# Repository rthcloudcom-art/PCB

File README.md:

# AgriNode — سخت‌افزار IoT برای مدیریت هوشمند کشاورزی و دامپروری

خانواده‌ای از بردهای الکترونیکی برای کنترل، مانیتورینگ و مدیریت **گلخانه، مرغداری، دامداری،
پرورش ماهی، مزرعه و باغ**.

| سند | محتوا |
|---|---|
| [`docs/01-features.md`](docs/01-features.md) | فاز ۱ — فهرست جامع قابلیت‌ها برای هر کاربری و ترجمه‌ی آن به نیازمندی سخت‌افزاری |
| [`docs/02-architecture.md`](docs/02-architecture.md) | فاز ۲ — معماری (نودها + هاب)، تغذیه، قوانین ساخت برای دستگاه کم‌دقت، اقدامات صنعتی |
| [`docs/03-roadmap.md`](docs/03-roadmap.md) | فاز ۳ — نقشه‌ی راه بردهای بعدی |
| [`docs/portfolio/`](docs/portfolio/README.md) | **سبد محصولات** (نسخه‌بندی‌شده) — کنترلر، برد قدرت، نود بی‌سیم، پروب هوشمند و راهکار ۱۵ صنعت؛ نسخه‌ی فعلی: v2 (در حال بررسی) |
| [`hardware/hubs/`](hardware/hubs/README.md) | **بردهای هاب** — HUB-W (Wi-Fi)، HUB-L (LoRa)، HUB-C (4G LTE)، GW-LAN (گیت‌وی LoRa→LAN)؛ هر کدام یک برد دو لایه‌ی جدا با هسته‌ی مشترک |
| [`hardware/lib/`](hardware/lib) | کتابخانه‌ی سمبل و فوت‌پرینت برای ساخت با دستگاه کم‌دقت (پدهای باریک‌شده، فاصله ≥ 0.55mm) |
| [`hardware/archive/mc1-4layer/`](hardware/archive/mc1-4layer/README.md) | نسخه‌ی قبلی (برد یکپارچه‌ی ۴ لایه، کنار گذاشته شد) |
| [`hardware/archive/hub1-universal-2layer/`](hardware/archive/hub1-universal-2layer/README.md) | نسخه‌ی قبلی هاب (یک برد برای همه‌ی انواع، کنار گذاشته شد) |

## ساختار مخزن

```
docs/                      اسناد نیازمندی و معماری
hardware/<board>/
    design/*.py            منبع طراحی مدار (پایتون)
    build.py               تولید شماتیک KiCad + بررسی نت‌لیست + BOM + PDF
    pcb.py                 تولید PCB (چیدمان، زون‌ها، قوانین، مسیریابی خودکار)
    kicad/                 پروژه‌ی KiCad تولیدشده
    outputs/               PDF شماتیک، BOM، گزارش DRC، تصاویر
tools/kigen/               کتابخانه‌ی کوچک «مدار به صورت کد» برای تولید فایل‌های KiCad
```

## پیش‌نیازها

- KiCad 7 یا جدیدتر (کتابخانه‌های رسمی symbol و footprint)
- Python 3.10+ (ماژول `pcbnew` که همراه KiCad نصب می‌شود)
- برای مسیریابی خودکار: Java 25 و [Freerouting](https://github.com/freerouting/freerouting) 2.4+
  (`FREEROUTING_JAR` و `FREEROUTING_JAVA` را تنظیم کنید)

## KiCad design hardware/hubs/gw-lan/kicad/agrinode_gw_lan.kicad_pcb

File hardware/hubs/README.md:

# بردهای هاب AgriNode (rev A)

هر نوع هاب یک **برد کوچک جداگانه** است. همه‌ی بردها یک **هسته‌ی مشترک** دارند (مدار و جای قطعات یکسان در
100 میلی‌متر سمت چپ برد) و فقط **بلوک ارتباطی** سمت راست برد فرق می‌کند. همه **دو لایه** با قوانین درشت
برای دستگاه کم‌دقت هستند (چرا دو لایه؟ [`docs/02-architecture.md`](../../docs/02-architecture.md#۵-چرا-بردهای-هاب-دو-لایه‌اند)).

| برد | پوشه | کاربرد | بلوک ارتباطی | ابعاد |
|---|---|---|---|---|
| **HUB-W** | [`hub-w/`](hub-w) | نودها ← Wi-Fi ← هاب ← Wi-Fi مودم | — (فقط هسته) | 114 × 96 mm |
| **HUB-L** | [`hub-l/`](hub-l) | هاب با ارسال LoRa به نقطه‌ی دور | Ra-02 (SX1278، 433MHz) | 130 × 96 mm |
| **HUB-C** | [`hub-c/`](hub-c) | هاب با سیم‌کارت 4G | هدر برد ماژول LTE (A7670E / EC200U) | 130 × 108 mm |
| **GW-LAN** | [`gw-lan/`](gw-lan) | گیرنده‌ی LoRa در ساختمان + کابل شبکه به مودم | Ra-02 + ENC28J60 + RJ45 | 150 × 108 mm |

آنتن PCB ماژول ESP32 حدود 6 میلی‌متر از لبه‌ی بالای برد بیرون می‌زند (برای برد Wi-Fi بهترین حالت است)؛
در جعبه جای آن را در نظر بگیرید.

## هسته‌ی مشترک

| بلوک | قطعه‌ی اصلی | توضیح |
|---|---|---|
| پردازنده | ESP32-WROOM-32E-N8 | Wi-Fi + BLE؛ ارتباط با نودها با ESP-NOW یا Wi-Fi |
| ورودی تغذیه | جک 5.5/2.1 و ترمینال 12V (7..24V)، ترمینال پنل خورشیدی 6..24V، USB-B 5V | هر ورودی: فیوز PTC، دیود معکوس، TVS |
| مبدل 5V | LM2596S-5 (ورودی 7..40V، 3A) | |
| شارژر | TP4056 (1A) + NTC دمای باتری | شارژ فقط بین 0 تا 45 درجه؛ بدون NTC جامپر `JP1` را لحیم کنید |
| باتری | 18650 **دارای مدار حفاظت** در جاباتری سوراخ‌دار | PTC + ماسفت حفاظت جاگذاری برعکس |
| مسیر توان | دیود + AO3401 | با وجود برق از 5V، در قطع برق بدون وقفه از باتری (UPS) |
| 3.3V | MIC29302 (افت ولتاژ کم، 3A) | |
| ساعت | **DS3231M** + باتری سکه‌ای CR2032 | زمان دقیق برای برچسب زمانی داده‌ها و زمان‌بندی، حتی بدون اینترنت و در قطع برق |
| پورت پروگرام | **USB-B** با CH340C + ریست/بوت خودکار | همان کابل USB هم برق می‌دهد هم پروگرام می‌کند (Arduino / ESP-IDF بدون فشار دکمه) |
| هدر PROG | 6 پین: `1 GND  2 TXD0  3 RXD0  4 3V3  5 EN  6 IO0` | برای مبدل USB-سریال بیرونی (مقاومت‌های 1k سری اجازه می‌دهند هدر بر CH340C غلبه کند) |
| دکمه‌ها | **RESET** و **BOOT / PAIR** (6×6 سوراخ‌دار) | BOOT هنگام روشن‌شدن = حالت پروگرام؛ در کار عادی = جفت‌سازی نود |
| LED وضعیت | هدر 4 پین برای **نوار LED آدرس‌پذیر WS2813** | پایین را ببینید |
| بازر | بازر مغناطیسی 5V با ترانزیستور | آلارم محلی |
| I²C | هدر 4 پین: `1 GND  2 3V3  3 SCL  4 SDA` | نمایشگر OLED یا سنسور اضافه |
| **RS-485 (اختیاری)** | MAX3485 + SM712 + ترمینال 3 پین | Modbus RTU برای سنسورهای صنعتی سیمی تا 1 km؛ اگر لازم نیست قطعات بلوک را لحیم نکنید (`bom_without_rs485.csv`) |

### چرا RTC و RS-485؟

- **RTC**: هاب داده‌ها را هنگام قطع اینترنت بافر می‌کند؛ بدون ساعت پشتیبان، بعد از قطع برق زمان داده‌ها گم
  می‌شود. DS3231M دقت ±5ppm دارد و با CR2032 سال‌ها کار می‌کند.
- **RS-485**: بسیاری از سنسورهای صنعتی (خاک 7-in-1، pH/EC، ایستگاه هواشناسی، کنتور برق، اینورتر) فقط
  Modbus RTU دارند؛ این کابل تا 1 کیلومتر در محیط پرنویز کار می‌کند. هاب می‌تواند سنسورهای نزدیک خودش را
  مستقیم بخواند. مقاومت پایان خط 120Ω با جامپر `JP2` (فقط روی آخرین دستگاه خط) وصل می‌شود.

### نوار LED وضعیت (WS2813)

هدر `LED STRIP WS2813`: `1 VLED  2 DIN  3 GND  4 GND`

- LEDها به صورت **نواری** پشت سر هم وصل می‌شوند (DO هر LED به DI بعدی) و روی پنل جعبه نصب می‌شوند.
- داده از GPIO27 با مبدل سطح BSS138 به 5V و مقاومت سری 330Ω؛ VLED از VSYS با فیوز PTC 0.75A
  (حدود 10 LED با حداکثر روشنایی سفید؛ برای وضعیت، روشنایی کم کافی است).
- WS2813 ورودی پشتیبان (BI) دارد: اگر یک LED خراب شود بقیه کار می‌کنند. BI اولین LED را به GND وصل کنید.
- هنگام کار با باتری، VLED حدود 3.3..4.2V است؛ WS2813 کار می‌کند ولی رنگ آبی/سفید کم‌نورتر است.

ترتیب پیشنهادی LEDها در فریم‌ور:

| LED | معنی | رنگ‌ها |
|---|---|---|
| 1 | تغذیه/باتری | سبز: برق شبکه · زرد: روی باتری · قرمز: باتری ضعیف · آبی چشمک‌زن: در حال شارژ |
| 2 | Wi-Fi و نودها | سبز: وصل · زرد: بعضی نودها قطع · قرمز: قطع |
| 3 | ارتباط بیرونی (Wi-Fi مودم / LoRa / 4G / LAN) | سبز: وصل · آبی چشمک: ارسال · قرمز: قطع |
| 4 | LoRa / LAN (فقط GW-LAN) | سبز چشمک: دریافت بسته · زرد: لینک LAN بدون اینترنت |
| 5 | آلارم | خاموش: عادی · قرمز چشمک: آلارم فعال |
| 6 | سیستم | سبز: عادی · بنفش: حالت جفت‌سازی · سفید: به‌روزرسانی فریم‌ور |

## بلوک‌های ارتباطی

### HUB-L و GW-LAN: LoRa

Ai-Thinker **Ra-02** (SX1278، 433MHz، تا 20dBm) روی SPI؛ آنتن با کابل IPEX به SMA روی جعبه.
GW-LAN در ساختمان قرار می‌گیرد، بسته‌های HUB-L را دریافت می‌کند و با **ENC28J60** (10BASE-T) و جک
مگنتیک HR911105A با کابل LAN به مودم می‌فرستد.

### HUB-C: برد ماژول 4G LTE

به‌جای لحیم ماژول سلولار روی برد (پدهای LGA ظریف که با دستگاه کم‌دقت قابل ساخت نیست)، یک **برد آماده‌ی
ماژول LTE** (برای کارخانه/محیط صنعتی: SIMCom **A7670E** یا Quectel **EC200U**، LTE Cat-1 با پشتیبانی 2G)
روی هدر 8 پین نصب می‌شود. این بردها سیم‌کارت، آنتن و مدار راه‌اندازی مودم را خودشان دارند.

هدر `LTE MODULE` (1×8، 2.54mm):

| پین | نام | توضیح |
|---|---|---|
| 1 | VMOD_5V | 5V قابل قطع (AO3401) — برای بردهایی که رگولاتور خودشان را دارند؛ فقط وقتی برق بیرونی وصل است |
| 2 | VMOD_4V | 4.0V / 3A قابل قطع (MIC29302، خازن 1000µF) — برای اتصال مستقیم به VBAT ماژول |
| 3، 4 | GND | |
| 5 | MOD_TXD | خروجی داده‌ی مودم ← GPIO19 (با 1k سری) |
| 6 | MOD_RXD | ورودی داده‌ی مودم ← GPIO23 (با 1k سری) |
| 7 | MOD_PWRKEY | کلید روشن/خاموش مودم (کلکتور باز، فعال-پایین) — GPIO21 |
| 8 | MOD_STATUS | وضعیت روشن‌بودن مودم ← GPIO18 |

- **فقط یکی** از پین‌های 1 یا 2 را به ورودی تغذیه‌ی برد ماژول وصل کنید (مطابق دیتاشیت همان برد).
- سطح منطقی UART باید **3.3V** باشد (بیشتر بردهای A7670E/EC200U مبدل سطح دارند؛ اگر پین سطح IO دارد
  آن را به 3.3V ببندید).
- ESP32 با GPIO22 تغذیه‌ی مودم را کامل قطع و وصل می‌کند (راه‌اندازی دوباره‌ی مودم هنگ‌کرده بدون حضور اپراتور).

## نقشه‌ی پایه‌های ESP32

پایه‌ها طوری انتخاب شده‌اند که هر سیگنال از سمتی از ماژول خارج شود که قطعه‌اش آنجاست (ستون راست ماژول رو به
RS-485 و بلوک ارتباطی، ستون چپ رو به تغذیه و پنل جلو، ردیف پایین رو به شارژر) تا مسیرها کوتاه و بدون تقاطع باشند.

**هسته (همه‌ی بردها):**

| GPIO | کاربرد | GPIO | کاربرد |
|---|---|---|---|
| 0 | دکمه BOOT/PAIR (+ ریست خودکار) | 27 | داده‌ی نوار LED |
| 1 / 3 | TX0 / RX0 (CH340C و هدر PROG) | 33 / 32 | I²C SDA / SCL (RTC و هدر I2C) |
| 2 | بازر | 34 | ولتاژ باتری (ADC) |
| 13 | وضعیت شارژ `CHRG` | 35 | ولتاژ ورودی DC/خورشیدی (ADC) |
| 17 / 16 / 4 | RS-485 TX / RX / DE | EN | ریست (دکمه، ریست خودکار، هدر PROG) |

**بلوک ارتباطی:**

| GPIO | HUB-L | GW-LAN | HUB-C |
|---|---|---|---|
| 18 | SPI SCK | SPI SCK | STATUS مودم (ورودی) |
| 19 | SPI MISO | SPI MISO | UART مودم RX |
| 23 | SPI MOSI | SPI MOSI | UART مودم TX |
| 5 | LoRa CS | LoRa CS | — |
| 21 | LoRa DIO0 | LoRa DIO0 | PWRKEY مودم |
| 22 | ریست LoRa | ENC28J60 CS | روشن‌کردن تغذیه‌ی مودم |
| 14 | — | ریست LoRa | — |
| 36 (VP) | — | وقفه‌ی ENC28J60 | — |

پایه‌های آزاد روی هر برد (مثلاً 12، 15، 25، 26، 39) برای توسعه‌ی بعدی خالی مانده‌اند.

## ساخت برد

- **دو لایه**، ضخامت 1.6mm، مس 35µm؛ ترک سیگنال 0.5mm، تغذیه 0.7..0.8mm، فاصله 0.5mm، ویا 0.6mm
  سوراخ / 1.2mm پد (اگر برد را خودتان می‌سازید، ویاها را با سیم مسی نازک از دو طرف لحیم کنید).
- همه‌ی قطعات در **سمت رو**؛ SMD فقط 1206، SOT-23، SOT-223، SOIC، TO-263 (بدون QFN/TSSOP/0603).
- صفحه‌ی زمین (GND pour) در هر دو لایه؛ زیر آنتن ESP32 مس و ترک ممنوع است.
- پس از مونتاژ و تست، **کوتینگ محافظ** (Conformal Coating) بزنید؛ کانکتورها، دکمه‌ها و هدرها را ماسک کنید.
- فایل‌های ساخت: `python3 export_fab.py <variant>` → `<variant>/outputs/fab/` و فایل zip.

## وضعیت فعلی PCB

| برد | مسیریابی | جامپر سیمی | DRC | خروجی‌ها |
|---|---|---|---|---|
| HUB-W | کامل | ندارد | 0 خطای فاصله/اتصال (فقط هشدار سیلک‌اسکرین و اسپوک حرارتی) | تصاویر + Gerber |
| HUB-L | کامل به‌جز 1 اتصال | **W1** (11 mm، مدار ریست خودکار: R19 پد 2 ← پایه‌ی بیس Q3) | 0 خطای فاصله | تصاویر + Gerber |
| HUB-C | کامل | ندارد | 0 خطای فاصله/اتصال | تصاویر + Gerber |
| GW-LAN | کامل | ندارد | 0 خطای فاصله/اتصال | تصاویر + Gerber |

**جامپر سیمی:** اتصالی که مسیریاب نتوانسته کامل کند با یک سیم روکش‌دار نازک (مثلاً سیم wire-wrap) در سمت رو
لحیم می‌شود؛ دو سر آن روی سیلک‌اسکرین با `W1`، `W2`… علامت خورده و فهرستش در `<variant>/outputs/jumpers.txt` است
(طبق توافق، حداکثر یکی دو جامپر).

**نکته‌ی هشدارهای DRC باقی‌مانده:** `silk_*` (متن سیلک نزدیک لبه یا روی هم) و `starved_thermal` (پد زمینی که
با یک اسپوک به صفحه‌ی زمین وصل شده) هیچ‌کدام اشکال الکتریکی نیستند. `lib_footprint_mismatch` روی جک RJ45 (و
در نسخه‌های قبلی USB-B) عمدی است: حلقه‌ی مسی پدهای سوراخ‌دار برای سوراخ‌کاری درشت به ≥ 0.26 mm بزرگ شده است.

## فایل‌ها

| مسیر | توضیح |
|---|---|
| `design/hubs.py` | منبع طراحی مدار (هسته + بلوک هر نوع) |
| `build.py <variant>` | تولید شماتیک KiCad، بررسی نت‌لیست، BOMها، PDF |
| `pcb.py <variant> [--route]` | چیدمان، قوانین، مسیریابی خودکار (Freerouting + مسیریاب تکمیلی)، DRC |
| `route_search.py <variant>` | چند تنظیم هزینه‌ی Freerouting را امتحان می‌کند و بهترین برد (کمترین اتصال باز، بدون خطای فاصله) را نگه می‌دارد |
| `render.py <variant>` | تصاویر `pcb_top.png`، `pcb_bottom.png`، `pcb_assembly.png` |
| `export_fab.py <variant>` | Gerber و Drill |
| `<variant>/kicad/` | پروژه‌ی KiCad (کتابخانه‌های `hardware/lib` از طریق جدول کتابخانه‌ی پروژه) |
| `<variant>/outputs/` | PDF شماتیک، `bom.csv` (ستون Option)، `bom_without_rs485.csv`، گزارش DRC، تصاویر، Gerber |

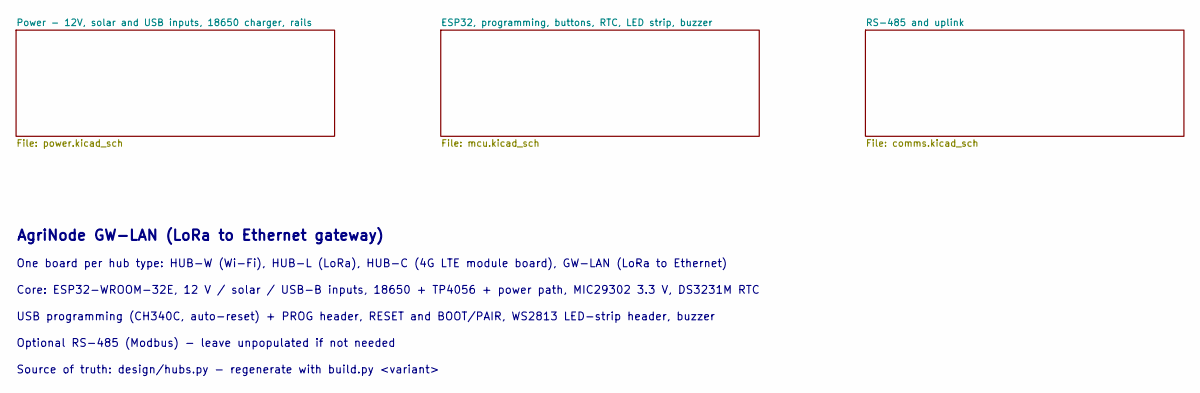
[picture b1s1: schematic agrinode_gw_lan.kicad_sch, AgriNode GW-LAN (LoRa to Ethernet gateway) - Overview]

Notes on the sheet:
AgriNode GW-LAN (LoRa to Ethernet gateway)
One board per hub type: HUB-W (Wi-Fi), HUB-L (LoRa), HUB-C (4G LTE module board), GW-LAN (LoRa to Ethernet)
Core: ESP32-WROOM-32E, 12 V / solar / USB-B inputs, 18650 + TP4056 + power path, MIC29302 3.3 V, DS3231M RTC
USB programming (CH340C, auto-reset) + PROG header, RESET and BOOT/PAIR, WS2813 LED-strip header, buzzer
Optional RS-485 (Modbus) - leave unpopulated if not needed
Source of truth: design/hubs.py - regenerate with build.py <variant>

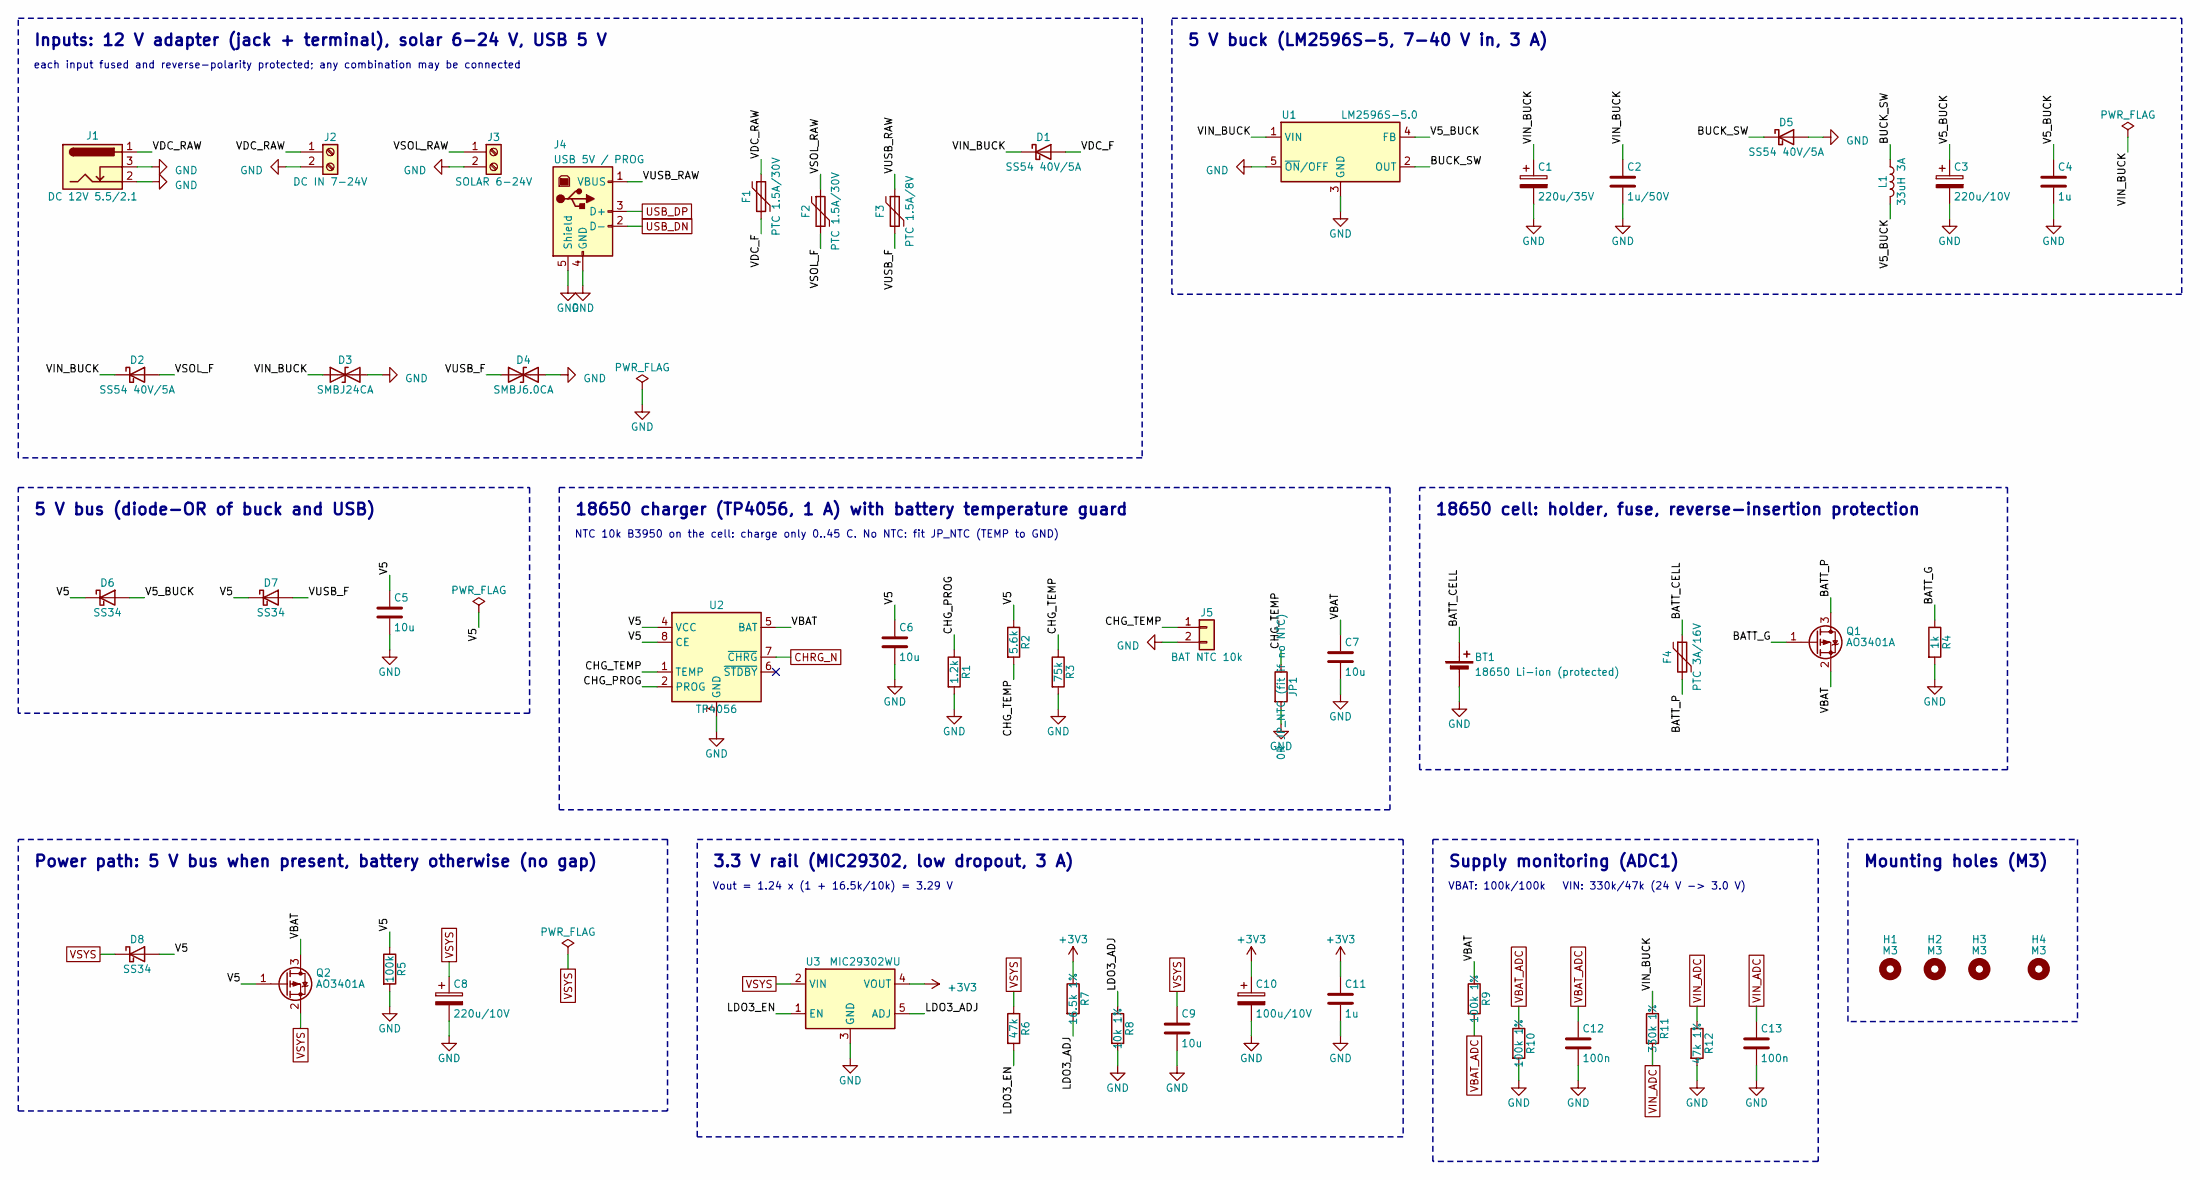
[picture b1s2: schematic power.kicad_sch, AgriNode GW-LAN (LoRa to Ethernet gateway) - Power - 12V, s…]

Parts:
BT1: 18650 Li-ion (protected); BatteryHolder_MPD_BH-18650-PC2
C1: 220u/35V; CP_Radial_D8.0mm_P3.50mm
C2: 1u/50V; C_1206_3216Metric
C3, C8: 220u/10V; CP_Radial_D8.0mm_P3.50mm
C4, C11: 1u; C_1206_3216Metric
C5, C6, C7, C9: 10u; C_1206_3216Metric
C10: 100u/10V; CP_Radial_D8.0mm_P3.50mm
C12, C13: 100n; C_1206_3216Metric
D1, D2, D5: SS54 40V/5A; D_SMC
D3: SMBJ24CA; D_SMB
D4: SMBJ6.0CA; D_SMB
D6, D7, D8: SS34; D_SMA
F1, F2: PTC 1.5A/30V; Fuse_1812_4532Metric
F3: PTC 1.5A/8V; Fuse_1812_4532Metric
F4: PTC 3A/16V; Fuse_1812_4532Metric
H1, H2, H3, H4: M3; MountingHole_3.2mm_M3
J1: DC 12V 5.5/2.1; BarrelJack_Horizontal
J2: DC IN 7-24V; TerminalBlock_Phoenix_MKDS-1,5-2-5.08_1x02_P5.08mm_Horizont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
J3: SOLAR 6-24V; TerminalBlock_Phoenix_MKDS-1,5-2-5.08_1x02_P5.08mm_Horizont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
J4: USB 5V / PROG; USB_B_THT_Coarse
J5: BAT NTC 10k; PinHeader_1x02_P2.54mm_Vertical
JP1: 0R JP_NTC (fit if no NTC); R_1206_3216Metric
L1: 33uH 3A; L_12x12mm_H6mm
Q1, Q2: AO3401A; SOT-23
R1: 1.2k; R_1206_3216Metric
R2: 5.6k; R_1206_3216Metric
R3: 75k; R_1206_3216Metric
R4: 1k; R_1206_3216Metric
R5: 100k; R_1206_3216Metric
R6: 47k; R_1206_3216Metric
R7: 16.5k 1%; R_1206_3216Metric
R8: 10k 1%; R_1206_3216Metric
R9, R10: 100k 1%; R_1206_3216Metric
R11: 330k 1%; R_1206_3216Metric
R12: 47k 1%; R_1206_3216Metric
U1: LM2596S-5.0; TO-263-5_TabPin3
U2: TP4056; ESOP-8_TP4056_Coarse
U3: MIC29302WU; TO-263-5_TabPin3

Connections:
+3V3: C10.1, C11.1, R7.1, U3.4 (VOUT); also elsewhere on the board
/Power - 12V, solar and USB inputs, 18650 charger, rails/BATT_CELL: BT1.1 (+), F4.1
/Power - 12V, solar and USB inputs, 18650 charger, rails/BATT_G: Q1.1 (G), R4.1
/Power - 12V, solar and USB inputs, 18650 charger, rails/BATT_P: F4.2, Q1.3 (D)
/Power - 12V, solar and USB inputs, 18650 charger, rails/BUCK_SW: D5.1 (K), L1.1, U1.2 (OUT)
/Power - 12V, solar and USB inputs, 18650 charger, rails/CHG_PROG: R1.1, U2.2 (PROG)
/Power - 12V, solar and USB inputs, 18650 charger, rails/CHG_TEMP: J5.1, JP1.1, R2.2, R3.1, U2.1 (TEMP)
/Power - 12V, solar and USB inputs, 18650 charger, rails/LDO3_ADJ: R7.2, R8.1, U3.5 (ADJ)
/Power - 12V, solar and USB inputs, 18650 charger, rails/LDO3_EN: R6.2, U3.1 (EN)
/Power - 12V, solar and USB inputs, 18650 charger, rails/V5: C5.1, C6.1, D6.1 (K), D7.1 (K), D8.2 (A), Q2.1 (G), R2.1, R5.1, U2.4 (VCC), U2.8 (CE)
/Power - 12V, solar and USB inputs, 18650 charger, rails/V5_BUCK: C3.1, C4.1, D6.2 (A), L1.2, U1.4 (FB)
/Power - 12V, solar and USB inputs, 18650 charger, rails/VBAT: C7.1, Q1.2 (S), Q2.3 (D), R9.1, U2.5 (BAT)
/Power - 12V, solar and USB inputs, 18650 charger, rails/VDC_F: D1.2 (A), F1.2
/Power - 12V, solar and USB inputs, 18650 charger, rails/VDC_RAW: F1.1, J1.1, J2.1
/Power - 12V, solar and USB inputs, 18650 charger, rails/VIN_BUCK: C1.1, C2.1, D1.1 (K), D2.1 (K), D3.1 (A1), R11.1, U1.1 (VIN)
/Power - 12V, solar and USB inputs, 18650 charger, rails/VSOL_F: D2.2 (A), F2.2
/Power - 12V, solar and USB inputs, 18650 charger, rails/VSOL_RAW: F2.1, J3.1
/Power - 12V, solar and USB inputs, 18650 charger, rails/VUSB_F: D4.1 (A1), D7.2 (A), F3.2
/Power - 12V, solar and USB inputs, 18650 charger, rails/VUSB_RAW: F3.1, J4.1 (VBUS)
CHRG_N: U2.7 (~CHRG); also elsewhere on the board
GND: BT1.2 (-), C1.2, C2.2, C3.2, C4.2, C5.2, C6.2, C7.2, C8.2, C9.2, C10.2, C11.2, C12.2, C13.2, D3.2 (A2), D4.2 (A2), D5.2 (A), J1.2, J1.3, J2.2, J3.2, J4.4 (GND), J4.5 (Shield), J5.2, JP1.2, R1.2, R3.2, R4.2, R5.2, R8.2, R10.2, R12.2, U1.3 (GND), U1.5 (~ON/OFF), U2.3 (GND), U2.9 (GND), U3.3 (GND); also elsewhere on the board
USB_DN: J4.2 (D-); also elsewhere on the board
USB_DP: J4.3 (D+); also elsewhere on the board
VBAT_ADC: C12.1, R9.2, R10.1; also elsewhere on the board
VIN_ADC: C13.1, R11.2, R12.1; also elsewhere on the board
VSYS: C8.1, C9.1, D8.1 (K), Q2.2 (S), R6.1, U3.2 (VIN); also elsewhere on the board

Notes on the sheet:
Inputs: 12 V adapter (jack + terminal), solar 6-24 V, USB 5 V
each input fused and reverse-polarity protected; any combination may be connected
5 V buck (LM2596S-5, 7-40 V in, 3 A)
5 V bus (diode-OR of buck and USB)
18650 charger (TP4056, 1 A) with battery temperature guard
NTC 10k B3950 on the cell: charge only 0..45 C. No NTC: fit JP_NTC (TEMP to GND)
18650 cell: holder, fuse, reverse-insertion protection
Power path: 5 V bus when present, battery otherwise (no gap)
3.3 V rail (MIC29302, low dropout, 3 A)
Vout = 1.24 x (1 + 16.5k/10k) = 3.29 V
Supply monitoring (ADC1)
VBAT: 100k/100k VIN: 330k/47k (24 V -> 3.0 V)
Mounting holes (M3)

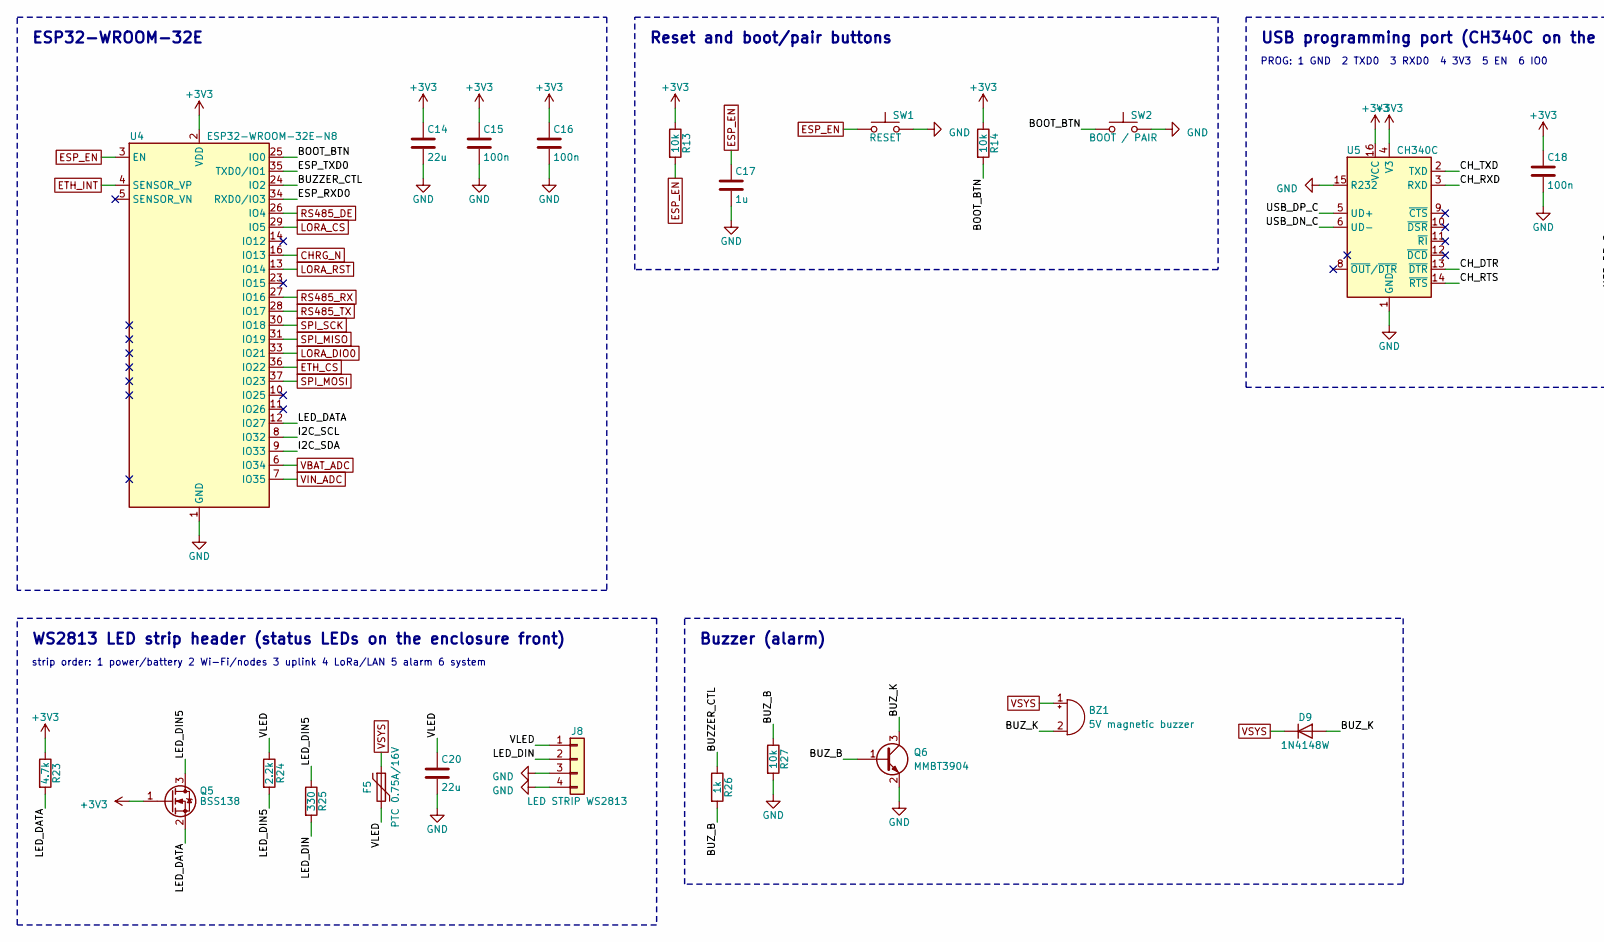
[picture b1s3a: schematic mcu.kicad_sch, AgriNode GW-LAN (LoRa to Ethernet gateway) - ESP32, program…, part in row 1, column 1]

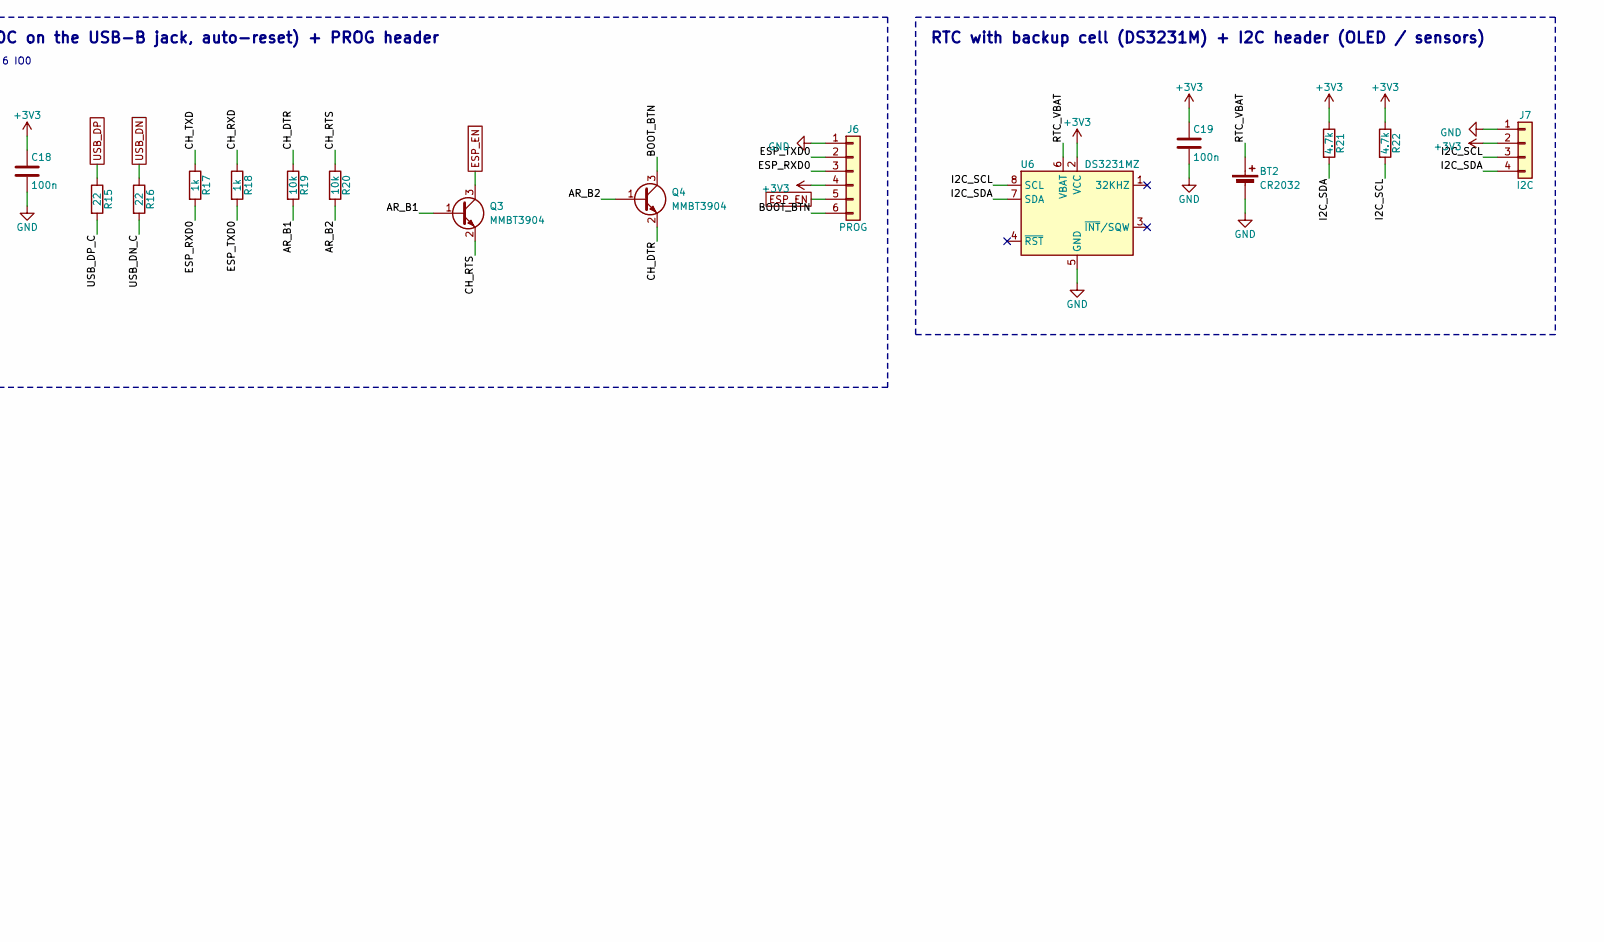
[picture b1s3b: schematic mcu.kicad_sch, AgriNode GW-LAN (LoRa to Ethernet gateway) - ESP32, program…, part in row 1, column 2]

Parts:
BT2: CR2032; BatteryHolder_Keystone_500
BZ1: 5V magnetic buzzer; Buzzer_12x9.5RM7.6
C14, C20: 22u; C_1206_3216Metric
C15, C16, C18, C19: 100n; C_1206_3216Metric
C17: 1u; C_1206_3216Metric
D9: 1N4148W; D_SOD-123
F5: PTC 0.75A/16V; Fuse_1812_4532Metric
J6: PROG; PinHeader_1x06_P2.54mm_Vertical
J7: I2C; PinHeader_1x04_P2.54mm_Vertical
J8: LED STRIP WS2813; PinHeader_1x04_P2.54mm_Vertical
Q3, Q4, Q6: MMBT3904; SOT-23
Q5: BSS138; SOT-23
R13, R14, R19, R20, R27: 10k; R_1206_3216Metric
R15, R16: 22; R_1206_3216Metric
R17, R18, R26: 1k; R_1206_3216Metric
R21, R22, R23: 4.7k; R_1206_3216Metric
R24: 2.2k; R_1206_3216Metric
R25: 330; R_1206_3216Metric
SW1: RESET; SW_PUSH_6mm
SW2: BOOT / PAIR; SW_PUSH_6mm
U4: ESP32-WROOM-32E-N8; ESP32-WROOM-32E_Coarse
U5: CH340C; SOIC-16_3.9x9.9mm_P1.27mm
U6: DS3231MZ; SOIC-8_3.9x4.9mm_P1.27mm

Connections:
+3V3: C14.1, C15.1, C16.1, C18.1, C19.1, J6.4, J7.2, Q5.1 (G), R13.1, R14.1, R21.1, R22.1, R23.1, U4.2 (VDD), U5.4 (V3), U5.16 (VCC), U6.2 (VCC); also elsewhere on the board
/ESP32, programming, buttons, RTC, LED strip, buzzer/AR_B1: Q3.1 (B), R19.2
/ESP32, programming, buttons, RTC, LED strip, buzzer/AR_B2: Q4.1 (B), R20.2
/ESP32, programming, buttons, RTC, LED strip, buzzer/BOOT_BTN: J6.6, Q4.3 (C), R14.2, SW2.1, U4.25 (IO0)
/ESP32, programming, buttons, RTC, LED strip, buzzer/BUZZER_CTL: R26.1, U4.24 (IO2)
/ESP32, programming, buttons, RTC, LED strip, buzzer/BUZ_B: Q6.1 (B), R26.2, R27.1
/ESP32, programming, buttons, RTC, LED strip, buzzer/BUZ_K: BZ1.2 (-), D9.2 (A), Q6.3 (C)
/ESP32, programming, buttons, RTC, LED strip, buzzer/CH_DTR: Q4.2 (E), R19.1, U5.13 (~DTR)
/ESP32, programming, buttons, RTC, LED strip, buzzer/CH_RTS: Q3.2 (E), R20.1, U5.14 (~RTS)
/ESP32, programming, buttons, RTC, LED strip, buzzer/CH_RXD: R18.1, U5.3 (RXD)
/ESP32, programming, buttons, RTC, LED strip, buzzer/CH_TXD: R17.1, U5.2 (TXD)
/ESP32, programming, buttons, RTC, LED strip, buzzer/ESP_RXD0: J6.3, R17.2, U4.34 (RXD0/IO3)
/ESP32, programming, buttons, RTC, LED strip, buzzer/ESP_TXD0: J6.2, R18.2, U4.35 (TXD0/IO1)
/ESP32, programming, buttons, RTC, LED strip, buzzer/I2C_SCL: J7.3, R22.2, U4.8 (IO32), U6.8 (SCL)
/ESP32, programming, buttons, RTC, LED strip, buzzer/I2C_SDA: J7.4, R21.2, U4.9 (IO33), U6.7 (SDA)
/ESP32, programming, buttons, RTC, LED strip, buzzer/LED_DATA: Q5.2 (S), R23.2, U4.12 (IO27)
/ESP32, programming, buttons, RTC, LED strip, buzzer/LED_DIN: J8.2, R25.2
/ESP32, programming, buttons, RTC, LED strip, buzzer/LED_DIN5: Q5.3 (D), R24.2, R25.1
/ESP32, programming, buttons, RTC, LED strip, buzzer/RTC_VBAT: BT2.1 (+), U6.6 (VBAT)
/ESP32, programming, buttons, RTC, LED strip, buzzer/USB_DN_C: R16.2, U5.6 (UD-)
/ESP32, programming, buttons, RTC, LED strip, buzzer/USB_DP_C: R15.2, U5.5 (UD+)
/ESP32, programming, buttons, RTC, LED strip, buzzer/VLED: C20.1, F5.2, J8.1, R24.1
CHRG_N: U4.16 (IO13); also elsewhere on the board
ESP_EN: C17.1, J6.5, Q3.3 (C), R13.2, SW1.1, U4.3 (EN); also elsewhere on the board
ETH_CS: U4.36 (IO22); also elsewhere on the board
ETH_INT: U4.4 (SENSOR_VP); also elsewhere on the board
GND: BT2.2 (-), C14.2, C15.2, C16.2, C17.2, C18.2, C19.2, C20.2, J6.1, J7.1, J8.3, J8.4, Q6.2 (E), R27.2, SW1.2, SW2.2, U4.1 (GND), U4.15 (GND), U4.38 (GND), U4.39 (GND), U5.1 (GND), U5.15 (R232), U6.5 (GND); also elsewhere on the board
LORA_CS: U4.29 (IO5); also elsewhere on the board
LORA_DIO0: U4.33 (IO21); also elsewhere on the board
LORA_RST: U4.13 (IO14); also elsewhere on the board
RS485_DE: U4.26 (IO4); also elsewhere on the board
RS485_RX: U4.27 (IO16); also elsewhere on the board
RS485_TX: U4.28 (IO17); also elsewhere on the board
SPI_MISO: U4.31 (IO19); also elsewhere on the board
SPI_MOSI: U4.37 (IO23); also elsewhere on the board
SPI_SCK: U4.30 (IO18); also elsewhere on the board
USB_DN: R16.1; also elsewhere on the board
USB_DP: R15.1; also elsewhere on the board
VBAT_ADC: U4.6 (IO34); also elsewhere on the board
VIN_ADC: U4.7 (IO35); also elsewhere on the board
VSYS: BZ1.1 (+), D9.1 (K), F5.1; also elsewhere on the board

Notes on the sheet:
ESP32-WROOM-32E
Reset and boot/pair buttons
USB programming port (CH340C on the USB-B jack, auto-reset) + PROG header
PROG: 1 GND 2 TXD0 3 RXD0 4 3V3 5 EN 6 IO0
RTC with backup cell (DS3231M) + I2C header (OLED / sensors)
WS2813 LED strip header (status LEDs on the enclosure front)
strip order: 1 power/battery 2 Wi-Fi/nodes 3 uplink 4 LoRa/LAN 5 alarm 6 system
Buzzer (alarm)

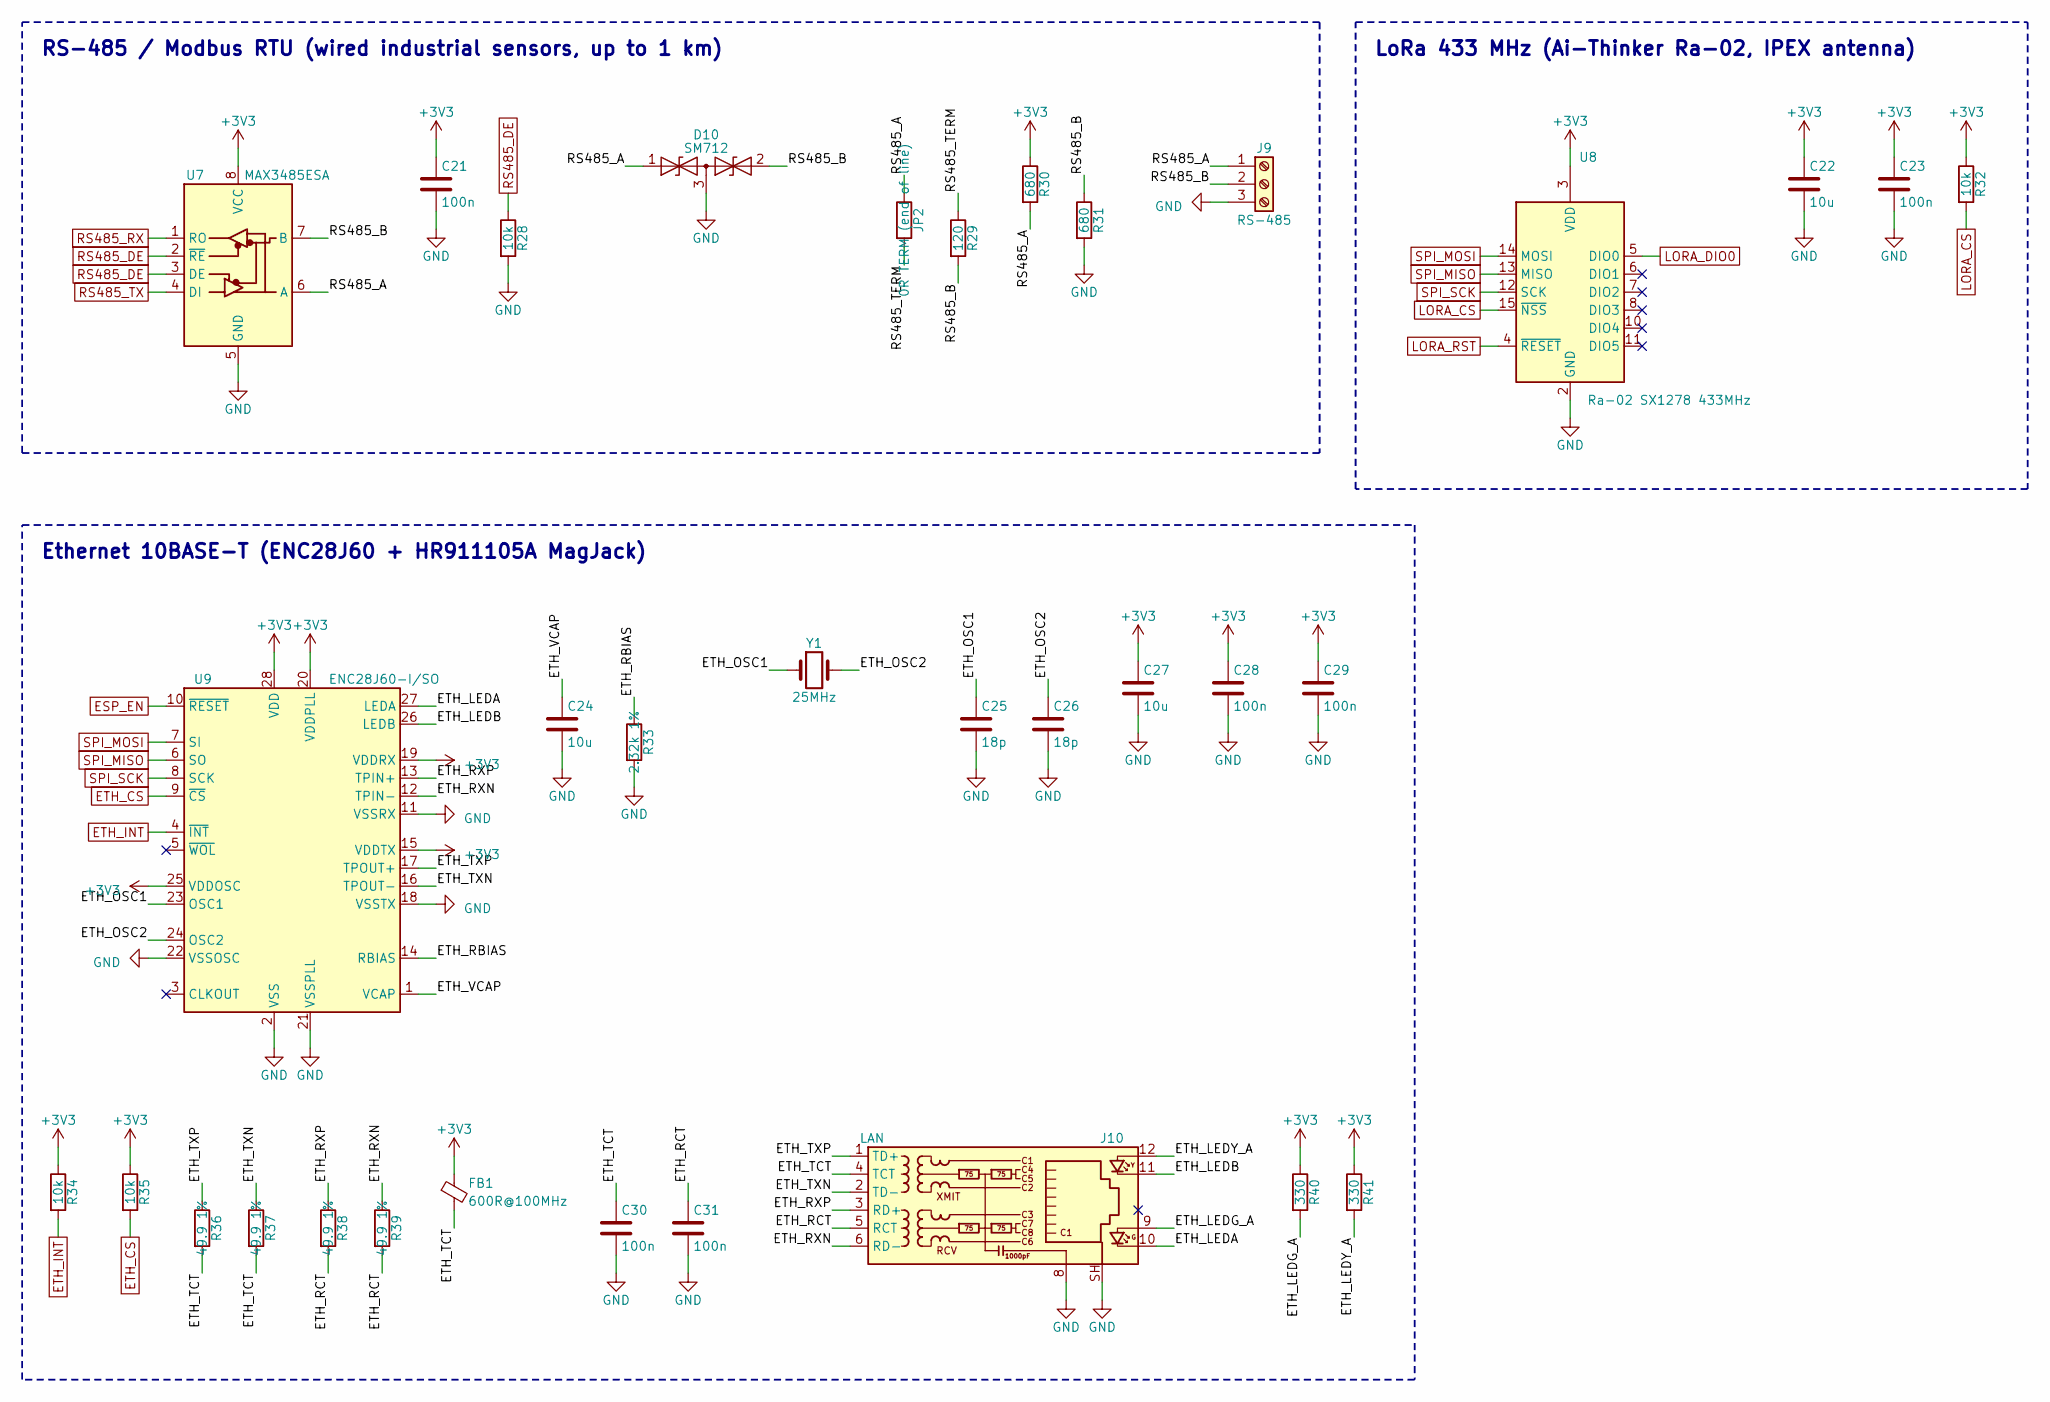
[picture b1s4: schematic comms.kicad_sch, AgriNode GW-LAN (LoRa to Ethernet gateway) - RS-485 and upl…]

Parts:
C21, C23, C28, C29, C30, C31: 100n; C_1206_3216Metric
C22, C24, C27: 10u; C_1206_3216Metric
C25, C26: 18p; C_1206_3216Metric
D10: SM712; SOT-23
FB1: 600R@100MHz; L_1206_3216Metric
J9: RS-485; TerminalBlock_Phoenix_MKDS-1,5-3-5.08_1x03_P5.08mm_Horizont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
J10: LAN; RJ45_Hanrun_HR911105A_Horizontal
JP2: 0R TERM (end of line); R_1206_3216Metric
R28, R32, R34, R35: 10k; R_1206_3216Metric
R29: 120; R_1206_3216Metric
R30, R31: 680; R_1206_3216Metric
R33: 2.32k 1%; R_1206_3216Metric
R36, R37, R38, R39: 49.9 1%; R_1206_3216Metric
R40, R41: 330; R_1206_3216Metric
U7: MAX3485ESA; SOIC-8_3.9x4.9mm_P1.27mm
U8: Ra-02 SX1278 433MHz; Ai-Thinker-Ra-02_Coarse
U9: ENC28J60-I/SO; SOIC-28W_7.5x17.9mm_P1.27mm
Y1: 25MHz; Crystal_HC49-4H_Vertical

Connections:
+3V3: C21.1, C22.1, C23.1, C27.1, C28.1, C29.1, FB1.1, R30.1, R32.1, R34.1, R35.1, R40.1, R41.1, U7.8 (VCC), U8.3 (VDD), U9.15 (VDDTX), U9.19 (VDDRX), U9.20 (VDDPLL), U9.25 (VDDOSC), U9.28 (VDD); also elsewhere on the board
/RS-485 and uplink/ETH_LEDA: J10.10, U9.27 (LEDA)
/RS-485 and uplink/ETH_LEDB: J10.11, U9.26 (LEDB)
/RS-485 and uplink/ETH_LEDG_A: J10.9, R40.2
/RS-485 and uplink/ETH_LEDY_A: J10.12, R41.2
/RS-485 and uplink/ETH_OSC1: C25.1, U9.23 (OSC1), Y1.1
/RS-485 and uplink/ETH_OSC2: C26.1, U9.24 (OSC2), Y1.2
/RS-485 and uplink/ETH_RBIAS: R33.1, U9.14 (RBIAS)
/RS-485 and uplink/ETH_RCT: C31.1, J10.5 (RCT), R38.2, R39.2
/RS-485 and uplink/ETH_RXN: J10.6 (RD-), R39.1, U9.12 (TPIN-)
/RS-485 and uplink/ETH_RXP: J10.3 (RD+), R38.1, U9.13 (TPIN+)
/RS-485 and uplink/ETH_TCT: C30.1, FB1.2, J10.4 (TCT), R36.2, R37.2
/RS-485 and uplink/ETH_TXN: J10.2 (TD-), R37.1, U9.16 (TPOUT-)
/RS-485 and uplink/ETH_TXP: J10.1 (TD+), R36.1, U9.17 (TPOUT+)
/RS-485 and uplink/ETH_VCAP: C24.1, U9.1 (VCAP)
/RS-485 and uplink/RS485_A: D10.1 (A1), J9.1, JP2.1, R30.2, U7.6 (A)
/RS-485 and uplink/RS485_B: D10.2 (A2), J9.2, R29.2, R31.1, U7.7 (B)
/RS-485 and uplink/RS485_TERM: JP2.2, R29.1
ESP_EN: U9.10 (~RESET); also elsewhere on the board
ETH_CS: R35.2, U9.9 (~CS); also elsewhere on the board
ETH_INT: R34.2, U9.4 (~INT); also elsewhere on the board
GND: C21.2, C22.2, C23.2, C24.2, C25.2, C26.2, C27.2, C28.2, C29.2, C30.2, C31.2, D10.3 (common), J9.3, J10.8, J10.SH, R28.2, R31.2, R33.2, U7.5 (GND), U8.1 (GND), U8.2 (GND), U8.9 (GND), U8.16 (GND), U9.2 (VSS), U9.11 (VSSRX), U9.18 (VSSTX), U9.21 (VSSPLL), U9.22 (VSSOSC); also elsewhere on the board
LORA_CS: R32.2, U8.15 (~NSS); also elsewhere on the board
LORA_DIO0: U8.5 (DIO0); also elsewhere on the board
LORA_RST: U8.4 (~RESET); also elsewhere on the board
RS485_DE: R28.1, U7.2 (~RE), U7.3 (DE); also elsewhere on the board
RS485_RX: U7.1 (RO); also elsewhere on the board
RS485_TX: U7.4 (DI); also elsewhere on the board
SPI_MISO: U8.13 (MISO), U9.6 (SO); also elsewhere on the board
SPI_MOSI: U8.14 (MOSI), U9.7 (SI); also elsewhere on the board
SPI_SCK: U8.12 (SCK), U9.8 (SCK); also elsewhere on the board

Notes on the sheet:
RS-485 / Modbus RTU (wired industrial sensors, up to 1 km)
LoRa 433 MHz (Ai-Thinker Ra-02, IPEX antenna)
Ethernet 10BASE-T (ENC28J60 + HR911105A MagJack)
